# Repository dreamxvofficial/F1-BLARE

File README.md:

# F1 BLARE 🏎️⏰

## Inspiration

I wanted to make a BLARE alarm clock, but I didn't want it to look like a normal alarm clock.

Since I really like Formula 1, I decided to design the enclosure around the shape and layout of an F1 steering wheel. The goal was to make something that looks like a small racing control system while still functioning as a practical alarm clock.

The display is placed in the center like the display on an F1 steering wheel, with four buttons around it for controlling the clock and alarms.

The four buttons are used for:

- `+`
- `Set Alarm / Stop Alarm`
- `-`
- `Change Screen`

There are four screens: the normal clock and three different alarm screens.

### Challenges

This was my first time making a PCB and working with KiCad, so there were quite a few things I had to figure out.

I had to learn how to make the schematic, assign footprints, route the PCB, check it with DRC and add 3D models.

One of the biggest challenges was designing the PCB so that all the components, buttons and display connections would fit into a compact enclosure.

I originally planned to use an F1 car model as part of the enclosure, but I changed the design so that the enclosure itself is F1-inspired and can be designed directly as a proper CAD model. This makes the final design easier to manufacture and 3D print.

### Specifications

BOM:

- 1x Seeed XIAO ESP32-C3
- 4x Cherry MX-style switches
- 1x 2.25" TFT display
- 1x 3.3V piezo buzzer
- 1x 8-pin connector for the display
- 8x female-female jumper wires
- 4x M3x8 screws
- 4x M3x16 screws
- 8x M3 heatset inserts

Others:

- Arduino firmware
- Custom PCB
- Custom F1 steering-wheel-inspired enclosure
- 3D printed enclosure

### How it works

The main screen shows the current time.

Pressing the fourth button changes between the clock and the three alarm screens.

On an alarm screen:

- `+` increases the alarm time
- `-` decreases the alarm time
- `Set Alarm` enables/disables the alarm

When an alarm goes off, the buzzer plays until the user presses the alarm button.

The enclosure is designed around an F1 steering wheel layout, with the TFT display positioned in the center and the four physical controls placed around it.

### Schematic

### PCB

| PCB | 3D Model |
| --- | --- |
|  |  |

### Case

The PCB will be mounted inside a custom 3D-printed enclosure inspired by an F1 steering wheel.

The 2.25" TFT display is positioned in the center of the front panel, with the four buttons arranged around it for easy access.

The enclosure will use rounded edges, racing-inspired shapes and details while keeping the internal geometry practical for 3D printing.

Unlike using an imported F1 car STL, the enclosure itself is designed as a proper CAD model so that the dimensions can be matched to the PCB and components.

### Firmware

The firmware is written using Arduino IDE and runs on the XIAO ESP32-C3.

The TFT display is controlled using the Adafruit GFX and ST7789 libraries.

The firmware handles:

- Digital clock display
- Three independent alarms
- Alarm time adjustment
- Alarm enable/disable
- Buzzer control
- Screen switching

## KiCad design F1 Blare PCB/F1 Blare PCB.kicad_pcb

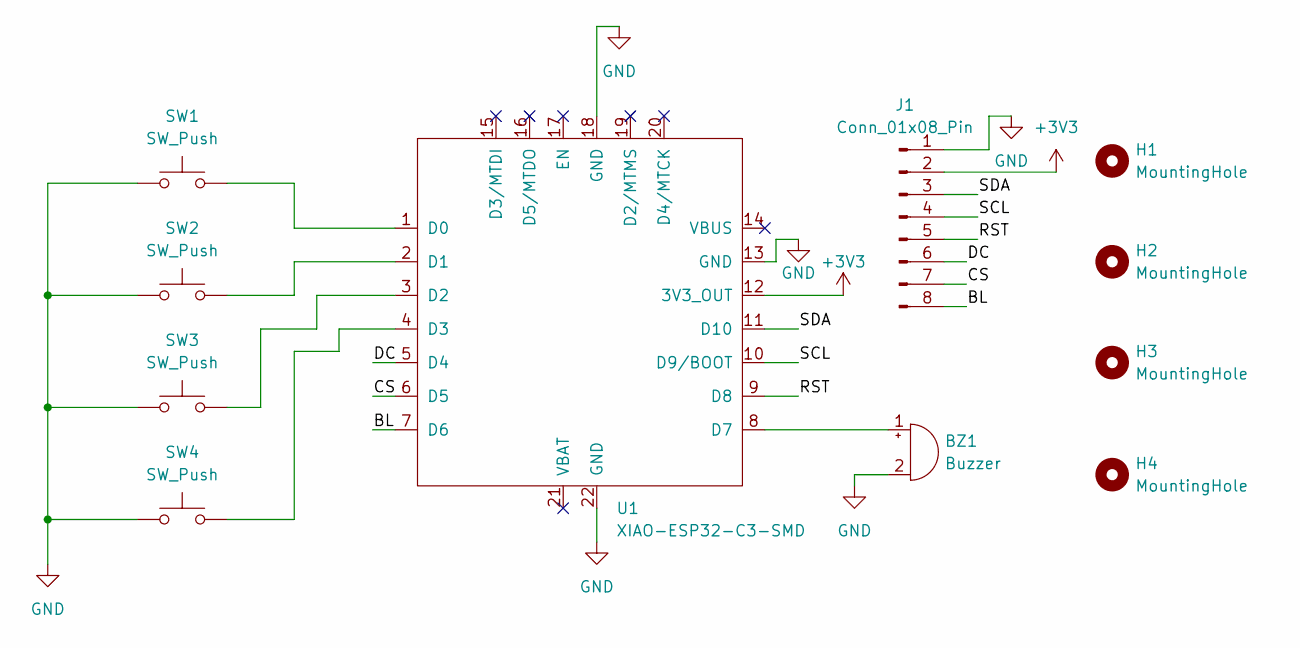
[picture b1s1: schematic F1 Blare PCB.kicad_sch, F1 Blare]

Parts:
BZ1: Buzzer; Buzzer_12x9.5RM7.6
H1, H2, H3, H4: MountingHole; MountingHole_3.2mm_M3
J1: Conn_01x08_Pin; PinSocket_1x08_P2.54mm_Vertical
SW1, SW2, SW3, SW4: SW_Push; SW_Cherry_MX_1.00u_PCB
U1: XIAO-ESP32-C3-SMD

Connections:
+3V3: J1.2, U1.12 (3V3_OUT)
/BL: J1.8, U1.7 (D6)
/CS: J1.7, U1.6 (D5)
/DC: J1.6, U1.5 (D4)
/RST: J1.5, U1.9 (D8)
/SCL: J1.4, U1.10 (D9/BOOT)
/SDA: J1.3, U1.11 (D10)
GND: BZ1.2 (-), J1.1, SW1.1, SW2.1, SW3.1, SW4.1, U1.13 (GND), U1.18 (GND), U1.22 (GND)
unnamed: BZ1.1 (+), U1.8 (D7)
unnamed: SW1.2, U1.1 (D0)
unnamed: SW2.2, U1.2 (D1)
unnamed: SW3.2, U1.3 (D2)
unnamed: SW4.2, U1.4 (D3)

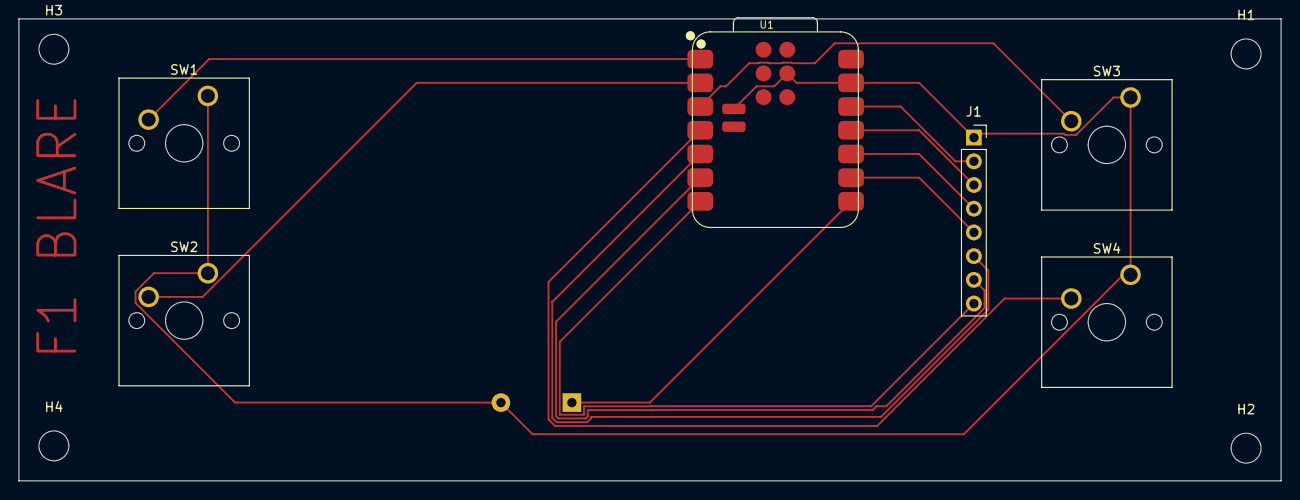
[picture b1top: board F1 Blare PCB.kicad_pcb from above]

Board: 2 copper layers, 135.2 x 49.5 mm, 11 parts (1 on the bottom side), 13 nets.
